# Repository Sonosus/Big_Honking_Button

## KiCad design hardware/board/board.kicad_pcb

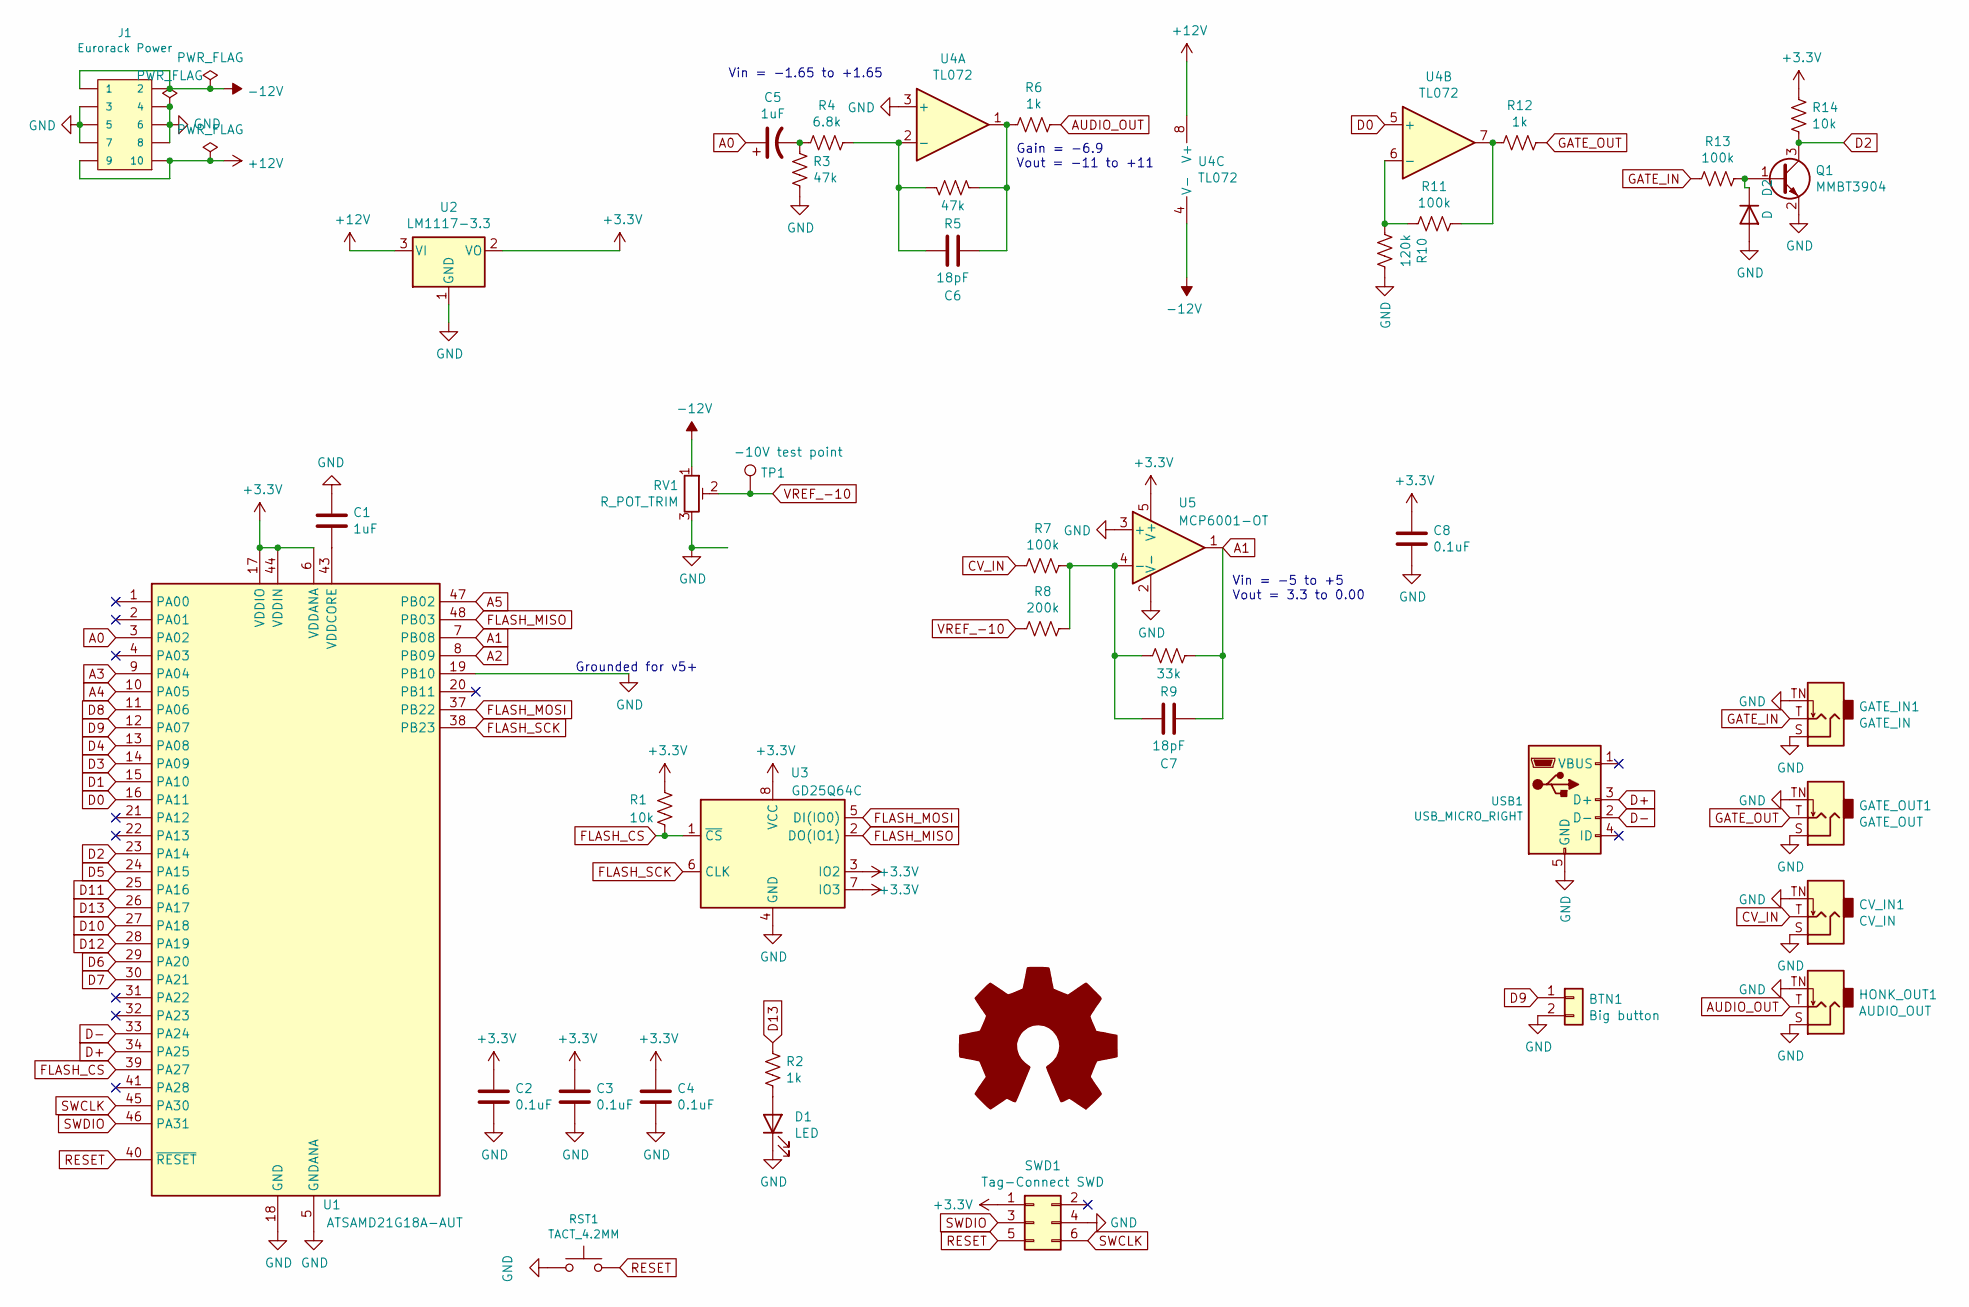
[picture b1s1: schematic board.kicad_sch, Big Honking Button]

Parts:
BTN1: Big button; PinHeader_1x02_P2.54mm_Vertical; mpn OBSF-30
C1: 1uF; Capacitor_NonPolarized; mpn MF-CAP-0603-1uF
C2, C3, C4, C8: 0.1uF; Capacitor_NonPolarizedSmall; mpn MF-CAP-0603-0.1uF
C5: 1uF; Capacitor_Polarized; mpn MF-CAP-0603-1uF
C6, C7: 18pF; Capacitor_NonPolarized; mpn MF-CAP-0603-18pF
CV_IN1: CV_IN; Jack_6.35mm_PJ_629HAN; mpn WQP-PJ398SM
D1: LED; LED_D5.0mm; mpn MF-LED-0603-GREEN
D2: D; Diode_DO-35; mpn MF-DIO-SOD123-1N4148
GATE_IN1: GATE_IN; Jack_6.35mm_PJ_629HAN; mpn WQP-PJ398SM
GATE_OUT1: GATE_OUT; Jack_6.35mm_PJ_629HAN; mpn WQP-PJ398SM
HONK_OUT1: AUDIO_OUT; Jack_6.35mm_PJ_629HAN; mpn WQP-PJ398SM
J1: Eurorack Power; Power_Header; mpn 61201021621
Q1: MMBT3904; Transistor_TO-92; mpn MF-DSC-SOT233-MMBT3904
R1, R14: 10k; Resistor; mpn MF-RES-0603-10K
R2: 1k; R_Axial_DIN0207_L6.3mm_D2.5mm_P2.54mm_Vertical; mpn MF-RES-0603-1K
R3, R5: 47k; Resistor; mpn ERA-3AED473V
R4: 6.8k; Resistor; mpn ERA-3AED682V
R6, R12: 1k; Resistor; mpn MF-RES-0603-1K
R7, R13: 100k; Resistor; mpn ERA-3AED104V
R8: 200k; Resistor; mpn ERA-3AEB204V
R9: 33k; Resistor; mpn ERA-3AED333V
R10: 120k; Resistor; mpn MF-RES-0603-1K
R11: 100k; Resistor; mpn MF-RES-0603-1K
RST1: TACT_4.2MM; PinHeader_1x02_P2.54mm_Vertical; mpn MF-SW-TACT-4.2MM
RV1: R_POT_TRIM; Potentiometer_Bourns_3296W_Vertical
SWD1: Tag-Connect SWD; PinHeader_2x03_P2.54mm_Vertical
TP1: -10V test point; TestPoint_Plated_Hole_D3.0mm
U1: ATSAMD21G18A-AUT; TQFP-48_7x7mm_P0.5mm; mpn ATSAMD21G18A-AUT
U2: LM1117-3.3; Regulator_TO-220-3
U3: GD25Q64C; SOIC-8_5.23x5.23mm_P1.27mm; mpn GD25Q64CSIGR
U4: TL072; DIP-8_Socket; mpn TL072CPWR
U5: MCP6001-OT; SOT-23-5; mpn MCP6001T-I/OT
USB1: USB_MICRO_RIGHT; Connector_USB_Micro_Tayda_A-5228; mpn MF-CON-MICROUSB-RIGHT

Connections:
+3V3: C2.1, C3.1, C4.1, C8.1, R1.1, R14.2, SWD1.1, U1.6 (VDDANA), U1.17 (VDDIO), U1.36 (VDDIO), U1.44 (VDDIN), U2.2 (VO), U3.3 (IO2), U3.7 (IO3), U3.8 (VCC), U5.5 (V+)
+12V: J1.9, J1.10, U2.3 (VI), U4.8 (V+)
-12V: J1.1, J1.2, RV1.1, U4.4 (V-)
A0: C5.1, U1.3 (PA02)
A1: C7.1, R9.1, U1.7 (PB08), U5.1
A2: U1.8 (PB09)
A3: U1.9 (PA04)
A4: U1.10 (PA05)
A5: U1.47 (PB02)
AUDIO_OUT: HONK_OUT1.T, R6.1
CV_IN: CV_IN1.T, R7.2
D0: U1.16 (PA11), U4.5 (+)
D1: U1.15 (PA10)
D2: Q1.3 (C), R14.1, U1.23 (PA14)
D3: U1.14 (PA09)
D4: U1.13 (PA08)
D5: U1.24 (PA15)
D6: U1.29 (PA20)
D7: U1.30 (PA21)
D8: U1.11 (PA06)
D9: BTN1.1, U1.12 (PA07)
D10: U1.27 (PA18)
D11: U1.25 (PA16)
D12: U1.28 (PA19)
D13: R2.2, U1.26 (PA17)
D+: U1.34 (PA25), USB1.3 (D+)
D-: U1.33 (PA24), USB1.2 (D-)
FLASH_CS: R1.2, U1.39 (PA27), U3.1 (~CS)
FLASH_MISO: U1.48 (PB03), U3.2 (DO(IO1))
FLASH_MOSI: U1.37 (PB22), U3.5 (DI(IO0))
FLASH_SCK: U1.38 (PB23), U3.6 (CLK)
GATE_IN: GATE_IN1.T, R13.2
GATE_OUT: GATE_OUT1.T, R12.1
GND: BTN1.2, C1.1, C2.2, C3.2, C4.2, C8.2, CV_IN1.S, CV_IN1.TN, D1.1 (K), D2.2 (A), GATE_IN1.S, GATE_IN1.TN, GATE_OUT1.S, GATE_OUT1.TN, HONK_OUT1.S, HONK_OUT1.TN, J1.3, J1.4, J1.5, J1.6, J1.7, J1.8, Q1.2 (E), R3.1, R10.1, RST1.1, RV1.3, SWD1.4, U1.5 (GNDANA), U1.18 (GND), U1.19 (PB10), U1.35 (GND), U1.42 (GND), U2.1 (GND), U3.4 (GND), U4.3 (+), U5.2 (V-), U5.3 (+), USB1.5 (GND)
unnamed: C1.2, U1.43 (VDDCORE)
unnamed: C5.2, R3.2, R4.2
unnamed: C6.1, R5.2, R6.2, U4.1
unnamed: C6.2, R4.1, R5.1, U4.2 (-)
unnamed: C7.2, R7.1, R8.1, R9.2, U5.4 (-)
unnamed: D1.2 (A), R2.1
unnamed: D2.1 (K), Q1.1 (B), R13.1
unnamed: R10.2, R11.2, U4.6 (-)
unnamed: R11.1, R12.2, U4.7
RESET: RST1.2, SWD1.5, U1.40 (~RESET)
SWCLK: SWD1.6, U1.45 (PA30)
SWDIO: SWD1.3, U1.46 (PA31)
VREF_-10: R8.2, RV1.2, TP1.1

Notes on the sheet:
Grounded for v5+
Vin = -1.65 to +1.65
Gain = -6.9 Vout = -11 to +11
Vin = -5 to +5 Vout = 3.3 to 0.00

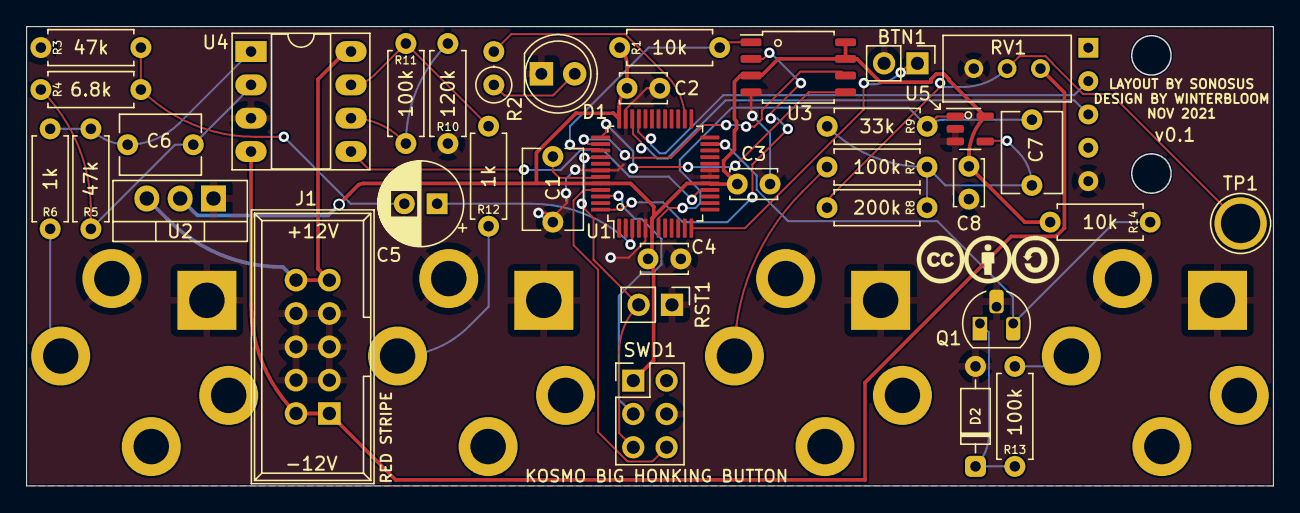
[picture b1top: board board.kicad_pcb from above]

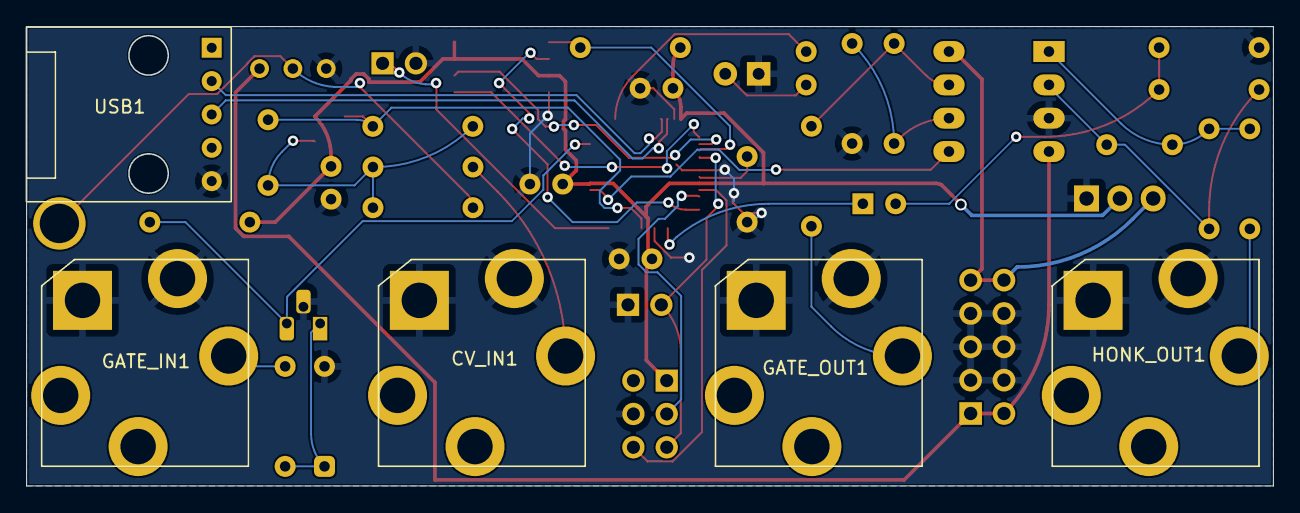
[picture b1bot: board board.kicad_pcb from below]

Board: 2 copper layers, 94.9 x 34.9 mm, 41 parts (5 on the bottom side), 33 nets.

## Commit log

2021-08-08 Use unused op amp to level shift and buffer gate output
2021-08-08 Diode to protect transistor
2021-11-18 done! apologies for no commits :-)
2021-11-18 update gitignore
2021-11-18 del redundant models

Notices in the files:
hardware/board/board.kicad_sch:
CC BY-SA 4.0
